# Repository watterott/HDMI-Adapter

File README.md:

# HDMI-Adapter
Universal HDMI/DVI Displays with Touch Panel based on an Adapter with TI TFP401 and Microchip ATmega32u4.

* [TI TFP401A](https://www.ti.com/product/TFP401A) HDMI to RGB Converter
* HDMI compatible (DVI, no Sound, no HDCP, no CEC)
* [Microchip ATmega32U4](https://www.microchip.com/wwwproducts/en/ATMEGA32U4) Microcontroller to control Backlight and Touch Panel (USB HID Mouse)
* LED Backlight Boost Regulator (up to 35V)
* Single 5V Power Supply via MicroUSB connector
* Open-Source and released under the [Creative Commons Attribution Share-Alike License](https://creativecommons.org/licenses/by-sa/4.0/).
* **[Documentation on learn.watterott.com](https://learn.watterott.com)**

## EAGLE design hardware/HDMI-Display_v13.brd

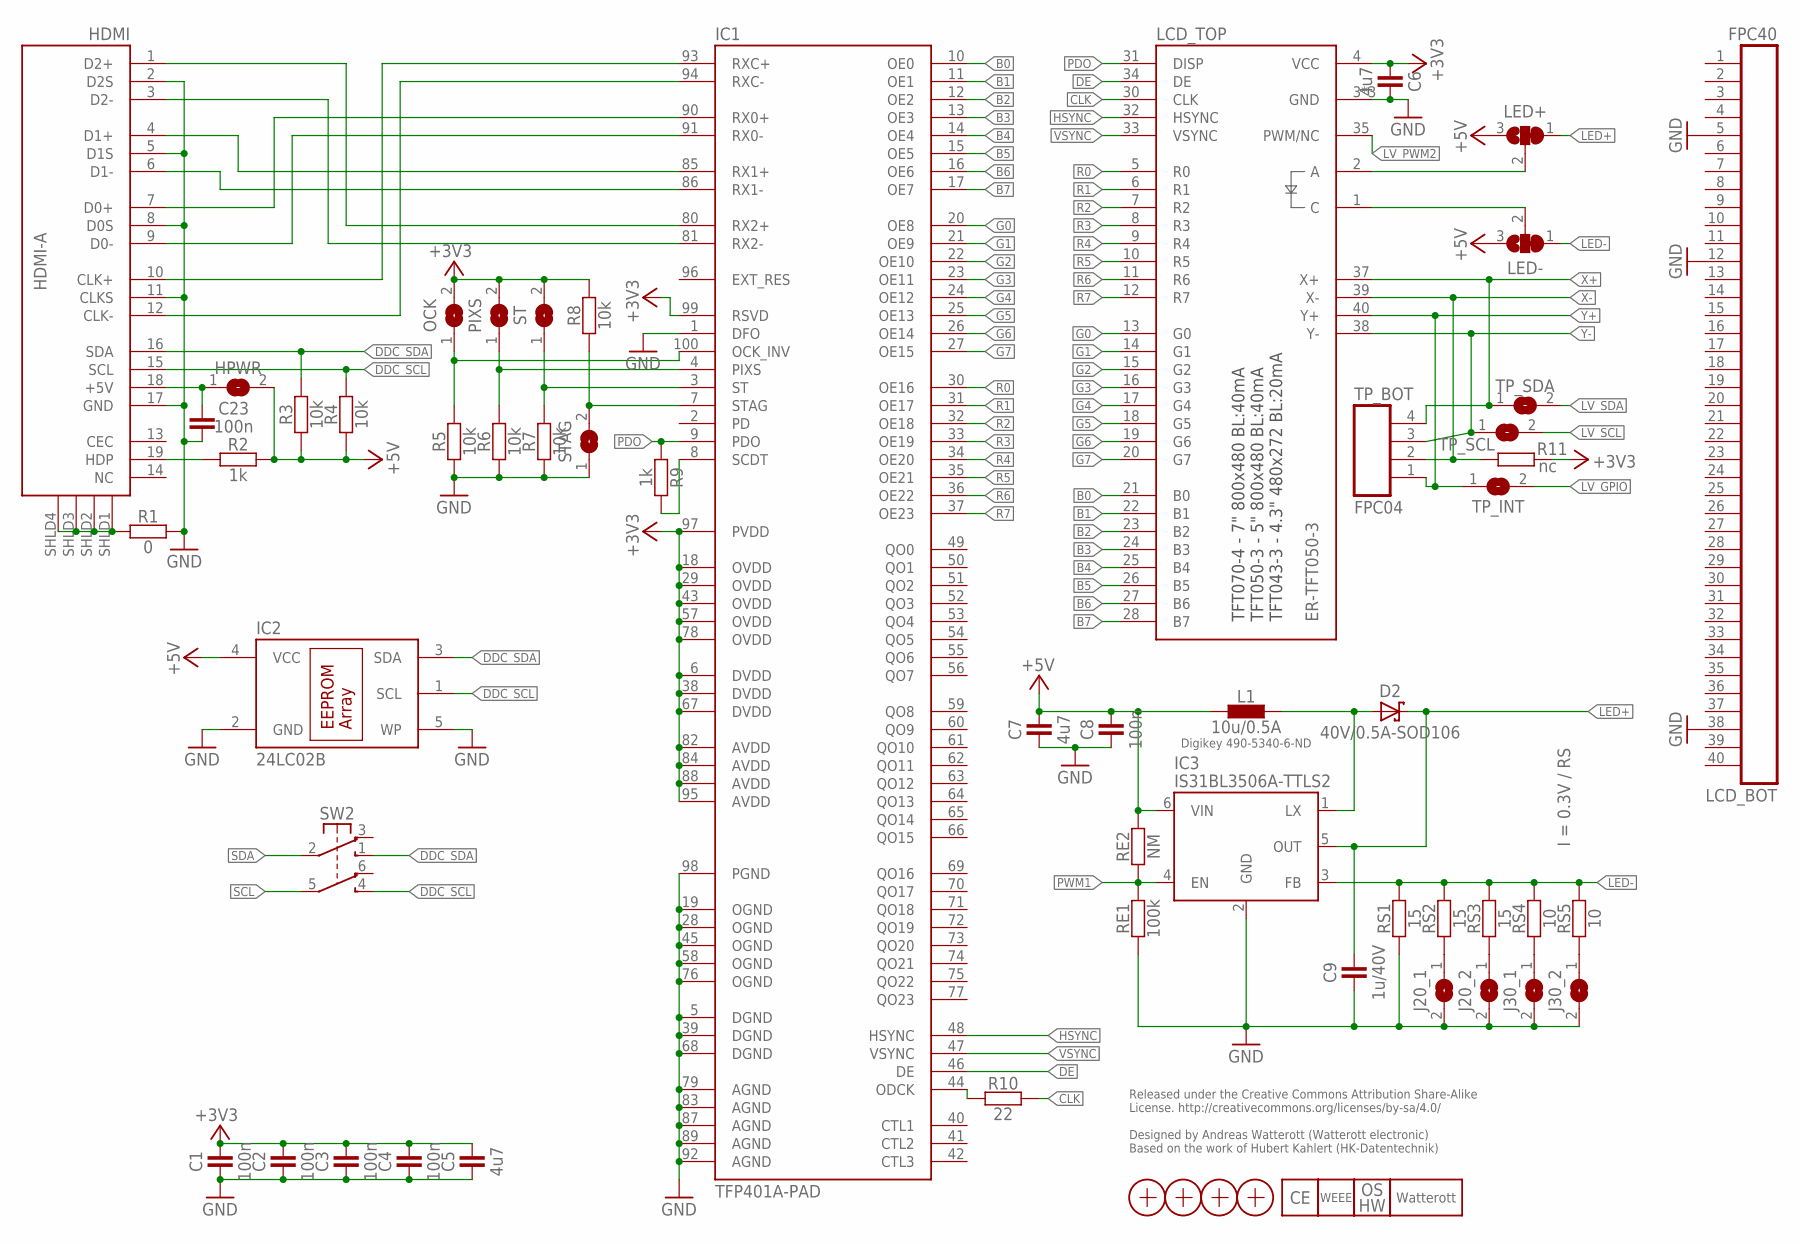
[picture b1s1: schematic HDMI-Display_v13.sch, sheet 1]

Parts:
C1, C2, C3, C4, C8, C23: 100n; C0402
C5, C6, C7: 4u7; C0402
C9: 1u/40V; C0805
D2: 40V/0.5A-SOD106; SOD106
HDMI: HDMI-A; HDMI_10029449
HPWR: JUMPER2-0402
IC1: TFP401A-PAD; TQFP100-PAD
IC2: 24LC02B; SOT23-5
IC3: IS31BL3506A-TTLS2; SOT23-6
J20_1, J20_2, J30_1, J30_2: JUMPER2-0402
L1: 10u/0.5A; L_1212
LCD_BOT: FPC40; FPC40-0.5
LCD_TOP: ER-TFT050-3; FPC40
LED+: JUMPER3-0402
LED-: JUMPER3-0402
LOGO2: LOGO_SPARK-2; SPARK_2MM
LOGO4: LOGO_WEEE-4; WEEE_4MM
LOGO5: LOGO_CE-2; CE_2MM
LOGO6: LOGO_OSHW-2; OSHW_2MM
OCK: JUMPER2-0201-NC; JUMPER2-0201_NC
PIXS: JUMPER2-0201-NC; JUMPER2-0201_NC
R1: 0; C0402
R2, R9: 1k; C0402
R3, R4, R5, R6, R7, R8: 10k; C0402
R10: 22; C0402
R11: nc; C0402
RE1: 100k; C0402
RE2: NM; C0402
RS1, RS2, RS3: 15; C0402
RS4, RS5: 10; C0402
ST: JUMPER2-0201-NC; JUMPER2-0201_NC
STAG: JUMPER2-0201-NC; JUMPER2-0201_NC
SW2: SW-2UM-CUS22B; CUS22B
TP_BOT: FPC04; FPC04-1.0
TP_INT: JUMPER2-0402
TP_SCL: JUMPER2-0402
TP_SDA: JUMPER2-0402
X1, X2, X3, X4: PASSER-07; PASSER_07MM

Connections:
+3V3: C1.2, C2.2, C3.2, C4.2, C5.2, C6.1, IC1.6 (DVDD), IC1.18 (OVDD), IC1.29 (OVDD), IC1.38 (DVDD), IC1.43 (OVDD), IC1.57 (OVDD), IC1.67 (DVDD), IC1.78 (OVDD), IC1.82 (AVDD), IC1.84 (AVDD), IC1.88 (AVDD), IC1.95 (AVDD), IC1.97 (PVDD), IC1.99 (RSVD), LCD_TOP.4 (VCC), OCK.2, PIXS.2, R8.2, R11.2, ST.2; also elsewhere on the board
+5V: C7.2, C8.2, HPWR.2, IC2.4 (VCC), IC3.6 (VIN), L1.1, LED+.3, LED-.3, R2.2, R3.1, R4.1, RE2.2; also elsewhere on the board
B0: IC1.10 (OE0), LCD_TOP.21 (B0)
B1: IC1.11 (OE1), LCD_TOP.22 (B1)
B2: IC1.12 (OE2), LCD_TOP.23 (B2)
B3: IC1.13 (OE3), LCD_TOP.24 (B3)
B4: IC1.14 (OE4), LCD_TOP.25 (B4)
B5: IC1.15 (OE5), LCD_TOP.26 (B5)
B6: IC1.16 (OE6), LCD_TOP.27 (B6)
B7: IC1.17 (OE7), LCD_TOP.28 (B7)
CLK: LCD_TOP.30 (CLK), R10.2
CLK_N: HDMI.12 (CLK-), IC1.94 (RXC-)
CLK_P: HDMI.10 (CLK+), IC1.93 (RXC+)
D0_N: HDMI.9 (D0-), IC1.91 (RX0-)
D0_P: HDMI.7 (D0+), IC1.90 (RX0+)
D1_N: HDMI.6 (D1-), IC1.86 (RX1-)
D1_P: HDMI.4 (D1+), IC1.85 (RX1+)
D2_N: HDMI.3 (D2-), IC1.81 (RX2-)
D2_P: HDMI.1 (D2+), IC1.80 (RX2+)
DDC_SCL: HDMI.15 (SCL), IC2.1 (SCL), R4.2, SW2.4 (S2)
DDC_SDA: HDMI.16 (SDA), IC2.3 (SDA), R3.2, SW2.1 (S1)
DE: IC1.46 (DE), LCD_TOP.34 (DE)
G0: IC1.20 (OE8), LCD_TOP.13 (G0)
G1: IC1.21 (OE9), LCD_TOP.14 (G1)
G2: IC1.22 (OE10), LCD_TOP.15 (G2)
G3: IC1.23 (OE11), LCD_TOP.16 (G3)
G4: IC1.24 (OE12), LCD_TOP.17 (G4)
G5: IC1.25 (OE13), LCD_TOP.18 (G5)
G6: IC1.26 (OE14), LCD_TOP.19 (G6)
G7: IC1.27 (OE15), LCD_TOP.20 (G7)
GND: C1.1, C2.1, C3.1, C4.1, C5.1, C6.2, C7.1, C8.1, C9.1, C23.1, HDMI.2 (D2S), HDMI.5 (D1S), HDMI.8 (D0S), HDMI.11 (CLKS), HDMI.17 (GND), IC1.1 (DFO), IC1.5 (DGND), IC1.19 (OGND), IC1.28 (OGND), IC1.39 (DGND), IC1.45 (OGND), IC1.58 (OGND), IC1.68 (DGND), IC1.76 (OGND), IC1.79 (AGND), IC1.83 (AGND), IC1.87 (AGND), IC1.89 (AGND), IC1.92 (AGND), IC1.98 (PGND), IC2.2 (GND), IC2.5 (WP), IC3.2 (GND), J20_1.2, J20_2.2, J30_1.2, J30_2.2, LCD_BOT.5, LCD_BOT.12, LCD_BOT.38, LCD_TOP.3 (GND), LCD_TOP.29 (GND), LCD_TOP.36 (GND), R1.1, R5.1, R6.1, R7.1, RE1.1, RS1.1, STAG.1; also elsewhere on the board
HDMI_5V: C23.2, HDMI.18 (+5V), HPWR.1
HDMI_DECT: HDMI.19 (HDP), R2.1
HSYNC: IC1.48 (HSYNC), LCD_TOP.32 (HSYNC)
LED+: C9.2, D2.C, IC3.5 (OUT), LED+.1
LED-: IC3.3 (FB), LED-.1, RS1.2, RS2.2, RS3.2, RS4.2, RS5.2
LEDA: LCD_TOP.2 (A), LED+.2
LEDC: LCD_TOP.1 (C), LED-.2
LV_GPIO: TP_INT.2; also elsewhere on the board
LV_PWM2: LCD_TOP.35 (PWM/NC); also elsewhere on the board
LV_SCL: TP_SCL.2; also elsewhere on the board
LV_SDA: TP_SDA.2; also elsewhere on the board
LX: D2.A, IC3.1 (LX), L1.2
unnamed: J20_2.1, RS3.1
unnamed: IC1.44 (ODCK), R10.1
unnamed: J30_1.1, RS4.1
unnamed: J20_1.1, RS2.1
unnamed: J30_2.1, RS5.1
OCKINV: IC1.100 (OCK_INV), OCK.1, R5.2
PDO: IC1.9 (PDO), LCD_TOP.31 (DISP), R9.1
PIXS: IC1.4 (PIXS), PIXS.1, R6.2
PWM1: IC3.4 (EN), RE1.2, RE2.1; also elsewhere on the board
R0: IC1.30 (OE16), LCD_TOP.5 (R0)
R1: IC1.31 (OE17), LCD_TOP.6 (R1)
R2: IC1.32 (OE18), LCD_TOP.7 (R2)
R3: IC1.33 (OE19), LCD_TOP.8 (R3)
R4: IC1.34 (OE20), LCD_TOP.9 (R4)
R5: IC1.35 (OE21), LCD_TOP.10 (R5)
R6: IC1.36 (OE22), LCD_TOP.11 (R6)
R7: IC1.37 (OE23), LCD_TOP.12 (R7)
SCDT: IC1.8 (SCDT), R9.2
SCL: SW2.5 (P2); also elsewhere on the board
SDA: SW2.2 (P1); also elsewhere on the board
SHLD3: HDMI.SHLD1 (SHLD), HDMI.SHLD2 (SHLD), HDMI.SHLD3 (SHLD), HDMI.SHLD4 (SHLD), R1.2
ST: IC1.3 (ST), R7.2, ST.1
STAG: IC1.7 (STAG), R8.1, STAG.2
VSYNC: IC1.47 (VSYNC), LCD_TOP.33 (VSYNC)
X+: LCD_TOP.37 (X+), TP_BOT.4, TP_SDA.1; also elsewhere on the board
X-: LCD_TOP.39 (X-), R11.1, TP_BOT.2; also elsewhere on the board
Y+: LCD_TOP.40 (Y+), TP_BOT.1, TP_INT.1; also elsewhere on the board
Y-: LCD_TOP.38 (Y-), TP_BOT.3, TP_SCL.1; also elsewhere on the board

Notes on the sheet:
I = 0.3V / RS
Digikey 490-5340-6-ND
Released under the Creative Commons Attribution Share-Alike License. http://creativecommons.org/licenses/by-sa/4.0/ Designed by Andreas Watterott (Watterott electronic) Based on the work of Hubert Kahlert (HK-Datentechnik)
TFT070-4 - 7" 800x480 BL:40mA TFT050-3 - 5" 800x480 BL:40mA TFT043-3 - 4.3" 480x272 BL:20mA

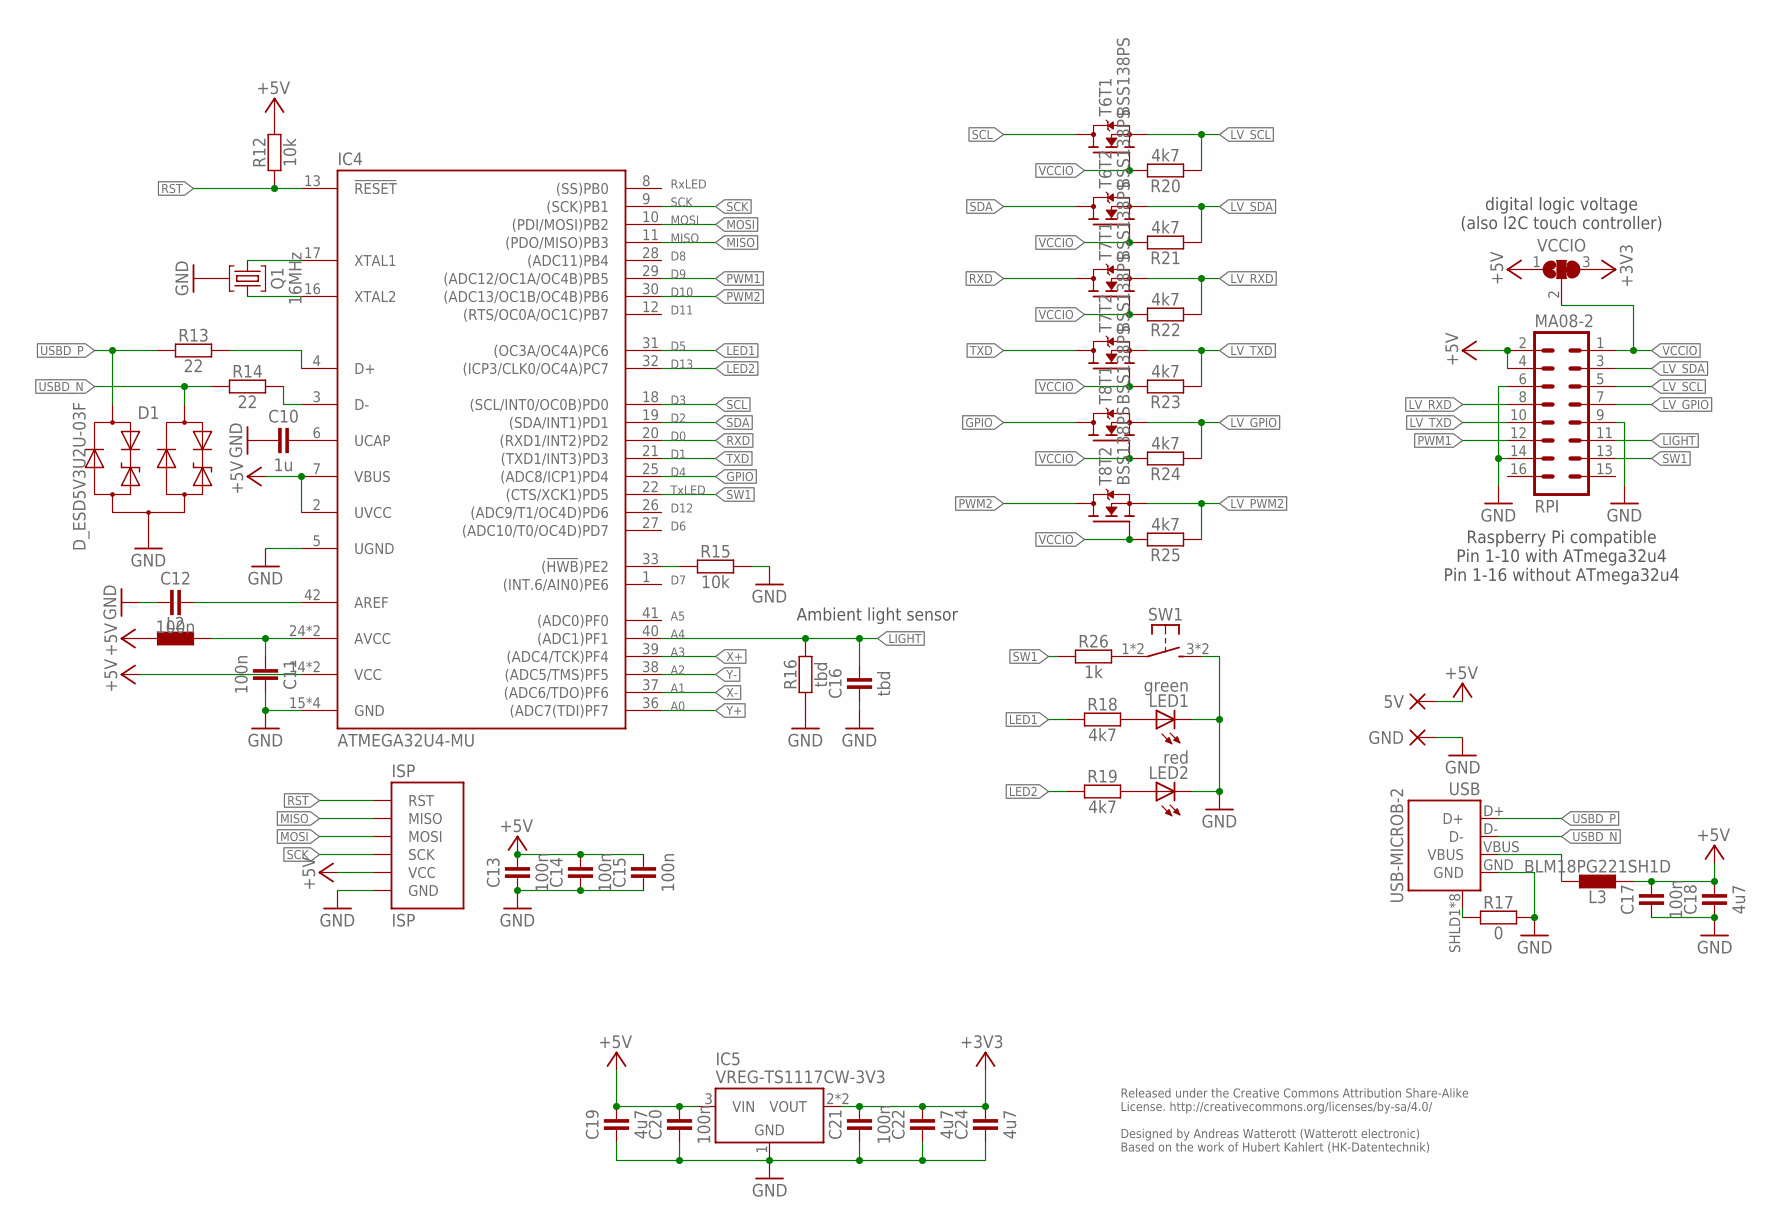
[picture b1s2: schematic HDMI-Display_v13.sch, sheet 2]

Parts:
5V: PAD-1.27X2.54_NC
C10: 1u; C0402
C11, C12, C13, C14, C15, C17, C20, C21: 100n; C0402
C16: tbd; C0402
C18, C19, C22, C24: 4u7; C0402
D1: D_ESD5V3U2U-03F; SOT723
GND: PAD-1.27X2.54_NC
IC4: ATMEGA32U4-MU; QFN44
IC5: VREG-TS1117CW-3V3; SOT223
ISP: ISP; ISP-2X3
L2: INDUCTOR-0603; C0603
L3: BLM18PG221SH1D; C0603
LED1: green; C0603
LED2: red; C0603
Q1: 16MHz; CRYSTAL_32X13
R12, R15: 10k; C0402
R13, R14: 22; C0402
R16: tbd; C0402
R17: 0; C0402
R18, R19, R20, R21, R22, R23, R24, R25: 4k7; C0402
R26: 1k; C0402
RPI: MA08-2
SW1: SW-TACTILE-PTS840P; PTS840P
T6, T7, T8: BSS138PS; SOT363
USB: USB-MICROB-2; USB-MICROB-10118194
VCCIO: JUMPER3-0402

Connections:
+3V3: C21.2, C22.2, C24.2, IC5.2 (VOUT), IC5.4 (VOUT), VCCIO.3; also elsewhere on the board
+5V: 5V.1, C13.2, C14.2, C15.2, C17.2, C18.2, C19.2, C20.2, IC4.2 (UVCC), IC4.7 (VBUS), IC4.14 (VCC), IC4.34 (VCC), IC5.3 (VIN), ISP.VCC, L2.1, L3.1, R12.2, RPI.2, RPI.4, VCCIO.1; also elsewhere on the board
AREF: C12.2, IC4.42 (AREF)
AVCC: C11.1, IC4.24 (AVCC), IC4.44 (AVCC), L2.2
D_N: IC4.3 (D-), R14.2
D_P: IC4.4 (D+), R13.2
GND: C10.1, C11.2, C12.1, C13.1, C14.1, C15.1, C16.1, C17.1, C18.1, C19.1, C20.1, C21.1, C22.1, C24.1, D1.3 (A), GND.1, IC4.5 (UGND), IC4.15 (GND), IC4.23 (GND), IC4.35 (GND), IC4.43 (GND), IC5.1 (GND), ISP.GND, LED1.C, LED2.C, Q1.GND, R15.2, R16.1, R17.1, RPI.6, RPI.9, RPI.14, SW1.3 (S1), SW1.4 (S1), USB.GND; also elsewhere on the board
GPIO: IC4.25 ((ADC8/ICP1)PD4), T8.6 (D)
HWB: IC4.33 ((!HWB!)PE2), R15.1
LED1: IC4.31 ((OC3A/OC4A)PC6), R18.1
LED2: IC4.32 ((ICP3/CLK0/OC4A)PC7), R19.1
LIGHT: C16.2, IC4.40 ((ADC1)PF1), R16.2, RPI.11
LV_GPIO: R24.1, RPI.7, T8.1 (S); also elsewhere on the board
LV_PWM2: R25.1, T8.4 (S); also elsewhere on the board
LV_RXD: R22.1, RPI.8, T7.1 (S)
LV_SCL: R20.1, RPI.5, T6.1 (S); also elsewhere on the board
LV_SDA: R21.1, RPI.3, T6.4 (S); also elsewhere on the board
LV_TXD: R23.1, RPI.10, T7.4 (S)
MISO: IC4.11 ((PDO/MISO)PB3), ISP.MISO
MOSI: IC4.10 ((PDI/MOSI)PB2), ISP.MOSI
unnamed: R26.2, SW1.1, SW1.2 (P1)
unnamed: LED1.A, R18.2
unnamed: LED2.A, R19.2
PWM1: IC4.29 ((ADC12/OC1A/OC4B)PB5), RPI.12; also elsewhere on the board
PWM2: IC4.30 ((ADC13/OC1B/OC4B)PB6), T8.3 (D)
RST: IC4.13 (!RESET), ISP.RST, R12.1
RXD: IC4.20 ((RXD1/INT2)PD2), T7.6 (D)
SCK: IC4.9 ((SCK)PB1), ISP.SCK
SCL: IC4.18 ((SCL/INT0/OC0B)PD0), T6.6 (D); also elsewhere on the board
SDA: IC4.19 ((SDA/INT1)PD1), T6.3 (D); also elsewhere on the board
SHLD1: R17.2, USB.SHLD1 (SHIELD), USB.SHLD2 (SHIELD), USB.SHLD3 (SHIELD), USB.SHLD4 (SHIELD), USB.SHLD5 (SHIELD), USB.SHLD6 (SHIELD), USB.SHLD7 (SHIELD), USB.SHLD8 (SHIELD)
SW1: IC4.22 ((CTS/XCK1)PD5), R26.1, RPI.13
TXD: IC4.21 ((TXD1/INT3)PD3), T7.3 (D)
UCAP: C10.2, IC4.6 (UCAP)
USBD_N: D1.2 (C2), R14.1, USB.D-
USBD_P: D1.1 (C1), R13.1, USB.D+
VBUS: L3.2, USB.VBUS
VCCIO: R20.2, R21.2, R22.2, R23.2, R24.2, R25.2, RPI.1, T6.2 (G), T6.5 (G), T7.2 (G), T7.5 (G), T8.2 (G), T8.5 (G), VCCIO.2
X+: IC4.39 ((ADC4/TCK)PF4); also elsewhere on the board
X-: IC4.37 ((ADC6/TDO)PF6); also elsewhere on the board
XTAL1: IC4.17 (XTAL1), Q1.2
XTAL2: IC4.16 (XTAL2), Q1.1
Y+: IC4.36 ((ADC7(TDI)PF7); also elsewhere on the board
Y-: IC4.38 ((ADC5/TMS)PF5); also elsewhere on the board

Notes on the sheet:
Ambient light sensor
Released under the Creative Commons Attribution Share-Alike License. http://creativecommons.org/licenses/by-sa/4.0/ Designed by Andreas Watterott (Watterott electronic) Based on the work of Hubert Kahlert (HK-Datentechnik)
TxLED
D12
D13
RxLED
SCK
MOSI
MISO
D10
D11
Raspberry Pi compatible Pin 1-10 with ATmega32u4 Pin 1-16 without ATmega32u4
digital logic voltage (also I2C touch controller)

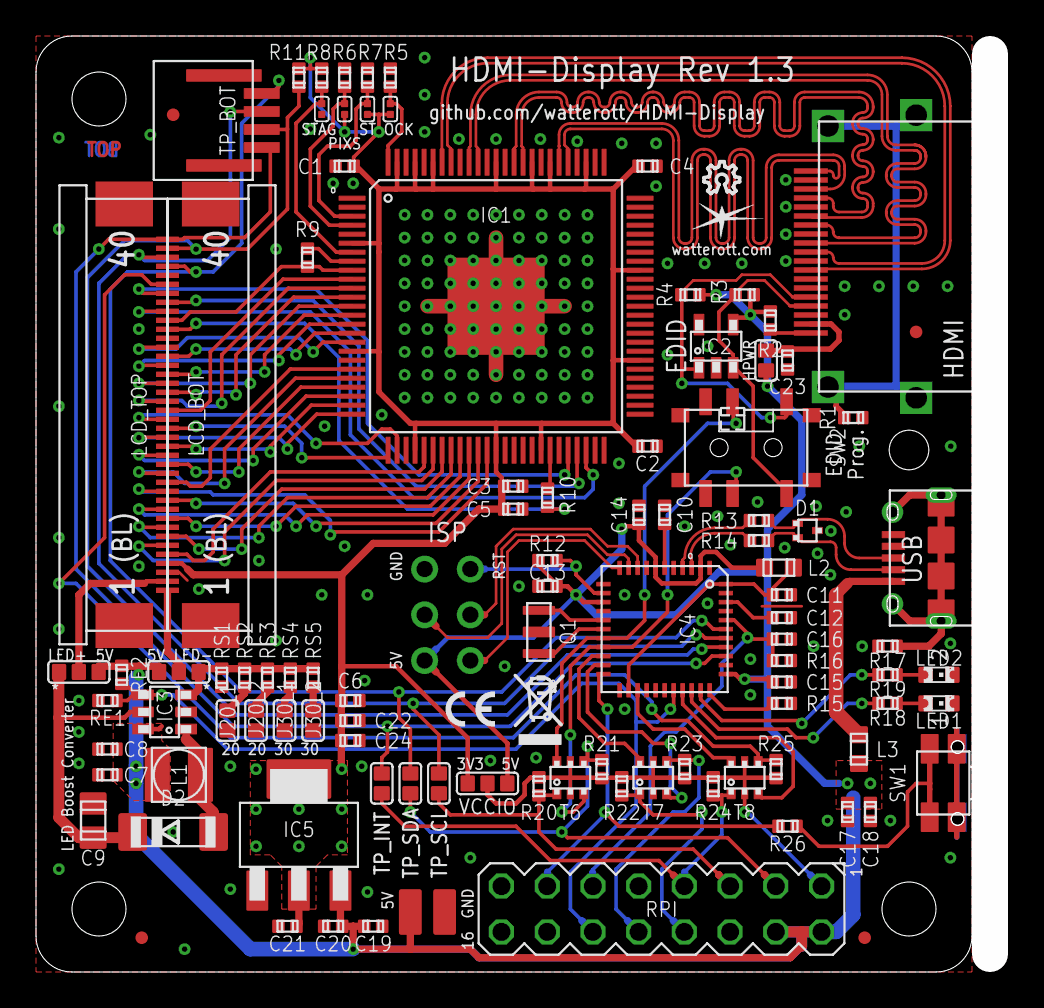
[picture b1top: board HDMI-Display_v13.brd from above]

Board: 2 copper layers, 52.0 x 50.0 mm, 107 parts (0 on the bottom side), 101 nets.

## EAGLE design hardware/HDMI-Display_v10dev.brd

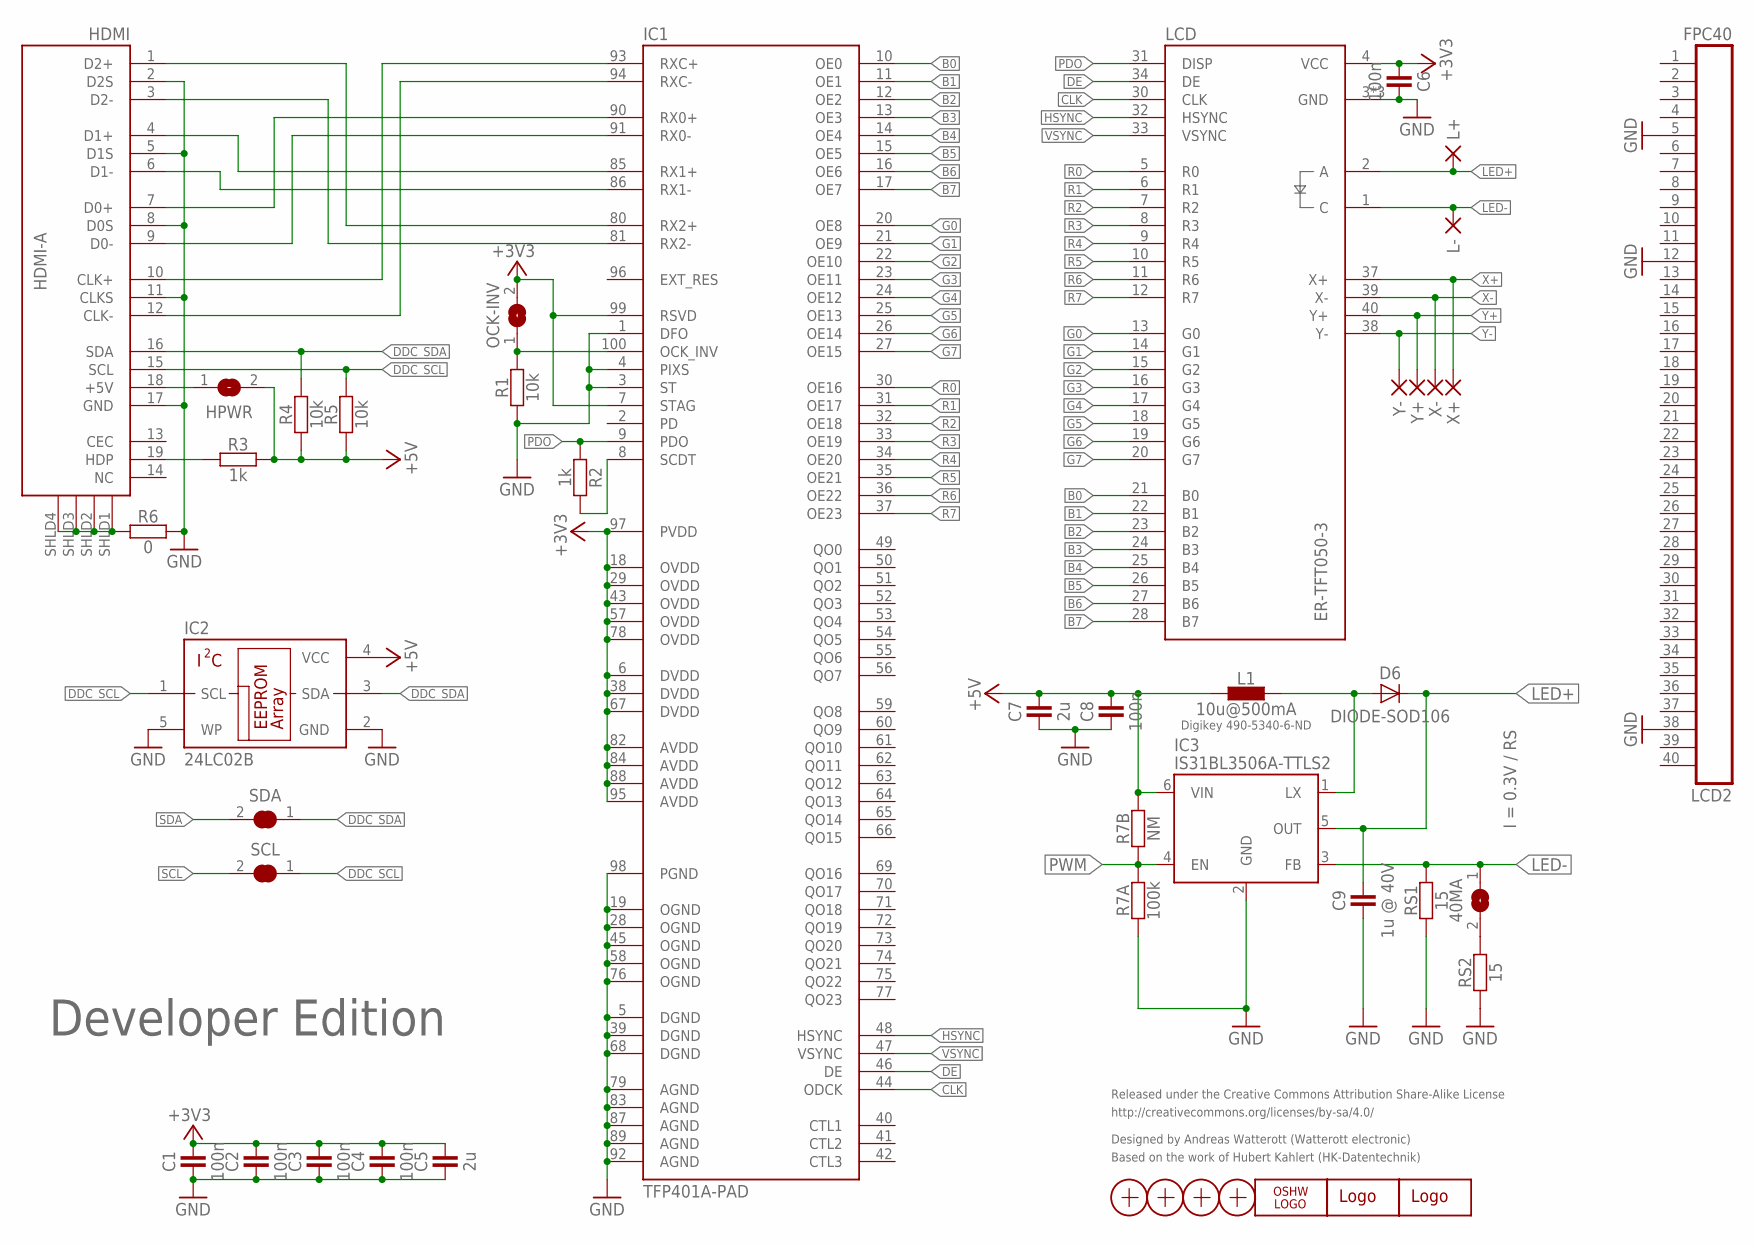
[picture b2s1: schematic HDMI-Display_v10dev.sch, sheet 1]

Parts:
40MA: JUMPER2
C1, C2, C3, C4, C6, C8: 100n; R0402
C5, C7: 2u; R0402
C9: 1u @ 40V; R0805
D6: DIODE-SOD106; SOD106
HDMI: HDMI-A; HDMI_10029449
HPWR: JUMPER2
IC1: TFP401A-PAD; TQFP100-PAD
IC2: 24LC02B; SOT23-5
IC3: IS31BL3506A-TTLS2; SOT23-6
L1: 10u@500mA; L_1212
L+: PAD-0.80X1.60_NC
L-: PAD-0.80X1.60_NC
LCD: ER-TFT050-3; FPC40
LCD2: FPC40
LOGO1: OSHW_LOGOX0070; OSHW_6X70
LOGO2: LOGO-PLACE; LOGO_TPLACE
LOGO3: LOGO-S_PLACE_S; SPARK_TPLACE_S
OCK-INV: JUMPER2
R1, R4, R5: 10k; R0402
R2, R3: 1k; R0402
R6: 0; R0402
R7A: 100k; R0402
R7B: NM; R0402
RS1, RS2: 15; R0402
SCL: JUMPER2
SDA: JUMPER2
X1, X2, X3, X4: PASSER-07; PASSER_07MM
X+: PAD-0.80X1.60_NC
X-: PAD-0.80X1.60_NC
Y+: PAD-0.80X1.60_NC
Y-: PAD-0.80X1.60_NC

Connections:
+3V3: C1.2, C2.2, C3.2, C4.2, C5.2, C6.1, IC1.6 (DVDD), IC1.7 (STAG), IC1.18 (OVDD), IC1.29 (OVDD), IC1.38 (DVDD), IC1.43 (OVDD), IC1.57 (OVDD), IC1.67 (DVDD), IC1.78 (OVDD), IC1.82 (AVDD), IC1.84 (AVDD), IC1.88 (AVDD), IC1.95 (AVDD), IC1.97 (PVDD), IC1.99 (RSVD), LCD.4 (VCC), OCK-INV.2; also elsewhere on the board
+5V: C7.2, C8.2, HPWR.2, IC2.4 (VCC), IC3.6 (VIN), L1.1, R3.2, R4.1, R5.1, R7B.2; also elsewhere on the board
B0: IC1.10 (OE0), LCD.21 (B0)
B1: IC1.11 (OE1), LCD.22 (B1)
B2: IC1.12 (OE2), LCD.23 (B2)
B3: IC1.13 (OE3), LCD.24 (B3)
B4: IC1.14 (OE4), LCD.25 (B4)
B5: IC1.15 (OE5), LCD.26 (B5)
B6: IC1.16 (OE6), LCD.27 (B6)
B7: IC1.17 (OE7), LCD.28 (B7)
CLK: IC1.44 (ODCK), LCD.30 (CLK)
CLK_N: HDMI.12 (CLK-), IC1.94 (RXC-)
CLK_P: HDMI.10 (CLK+), IC1.93 (RXC+)
D0_N: HDMI.9 (D0-), IC1.91 (RX0-)
D0_P: HDMI.7 (D0+), IC1.90 (RX0+)
D1_N: HDMI.6 (D1-), IC1.86 (RX1-)
D1_P: HDMI.4 (D1+), IC1.85 (RX1+)
D2_N: HDMI.3 (D2-), IC1.81 (RX2-)
D2_P: HDMI.1 (D2+), IC1.80 (RX2+)
DDC_SCL: HDMI.15 (SCL), IC2.1 (SCL), R5.2, SCL.1
DDC_SDA: HDMI.16 (SDA), IC2.3 (SDA), R4.2, SDA.1
DE: IC1.46 (DE), LCD.34 (DE)
G0: IC1.20 (OE8), LCD.13 (G0)
G1: IC1.21 (OE9), LCD.14 (G1)
G2: IC1.22 (OE10), LCD.15 (G2)
G3: IC1.23 (OE11), LCD.16 (G3)
G4: IC1.24 (OE12), LCD.17 (G4)
G5: IC1.25 (OE13), LCD.18 (G5)
G6: IC1.26 (OE14), LCD.19 (G6)
G7: IC1.27 (OE15), LCD.20 (G7)
GND: C1.1, C2.1, C3.1, C4.1, C5.1, C6.2, C7.1, C8.1, C9.1, HDMI.2 (D2S), HDMI.5 (D1S), HDMI.8 (D0S), HDMI.11 (CLKS), HDMI.17 (GND), IC1.1 (DFO), IC1.3 (ST), IC1.4 (PIXS), IC1.5 (DGND), IC1.19 (OGND), IC1.28 (OGND), IC1.39 (DGND), IC1.45 (OGND), IC1.58 (OGND), IC1.68 (DGND), IC1.76 (OGND), IC1.79 (AGND), IC1.83 (AGND), IC1.87 (AGND), IC1.89 (AGND), IC1.92 (AGND), IC1.98 (PGND), IC2.2 (GND), IC2.5 (WP), IC3.2 (GND), LCD.3 (GND), LCD.29 (GND), LCD.36 (GND), LCD2.5, LCD2.12, LCD2.38, R1.1, R6.1, R7A.1, RS1.1, RS2.1; also elsewhere on the board
HDMI_5V: HDMI.18 (+5V), HPWR.1
HDMI_DECT: HDMI.19 (HDP), R3.1
HSYNC: IC1.48 (HSYNC), LCD.32 (HSYNC)
LED+: C9.2, D6.C, IC3.5 (OUT), L+.1, LCD.2 (A)
LED-: 40MA.1, IC3.3 (FB), L-.1, LCD.1 (C), RS1.2
LX: D6.A, IC3.1 (LX), L1.2
unnamed: 40MA.2, RS2.2
unnamed: IC1.100 (OCK_INV), OCK-INV.1, R1.2
PDO: IC1.9 (PDO), LCD.31 (DISP), R2.1
PWM: IC3.4 (EN), R7A.2, R7B.1; also elsewhere on the board
R0: IC1.30 (OE16), LCD.5 (R0)
R1: IC1.31 (OE17), LCD.6 (R1)
R2: IC1.32 (OE18), LCD.7 (R2)
R3: IC1.33 (OE19), LCD.8 (R3)
R4: IC1.34 (OE20), LCD.9 (R4)
R5: IC1.35 (OE21), LCD.10 (R5)
R6: IC1.36 (OE22), LCD.11 (R6)
R7: IC1.37 (OE23), LCD.12 (R7)
SCDT: IC1.8 (SCDT), R2.2
SCL: SCL.2; also elsewhere on the board
SDA: SDA.2; also elsewhere on the board
SHLD3: HDMI.SHLD1 (SHLD), HDMI.SHLD2 (SHLD), HDMI.SHLD3 (SHLD), HDMI.SHLD4 (SHLD), R6.2
VSYNC: IC1.47 (VSYNC), LCD.33 (VSYNC)
X+: LCD.37 (X+), X+.1; also elsewhere on the board
X-: LCD.39 (X-), X-.1; also elsewhere on the board
Y+: LCD.40 (Y+), Y+.1; also elsewhere on the board
Y-: LCD.38 (Y-), Y-.1; also elsewhere on the board

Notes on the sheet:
I = 0.3V / RS
Digikey 490-5340-6-ND
Released under the Creative Commons Attribution Share-Alike License
http://creativecommons.org/licenses/by-sa/4.0/
Designed by Andreas Watterott (Watterott electronic)
Based on the work of Hubert Kahlert (HK-Datentechnik)
Developer Edition

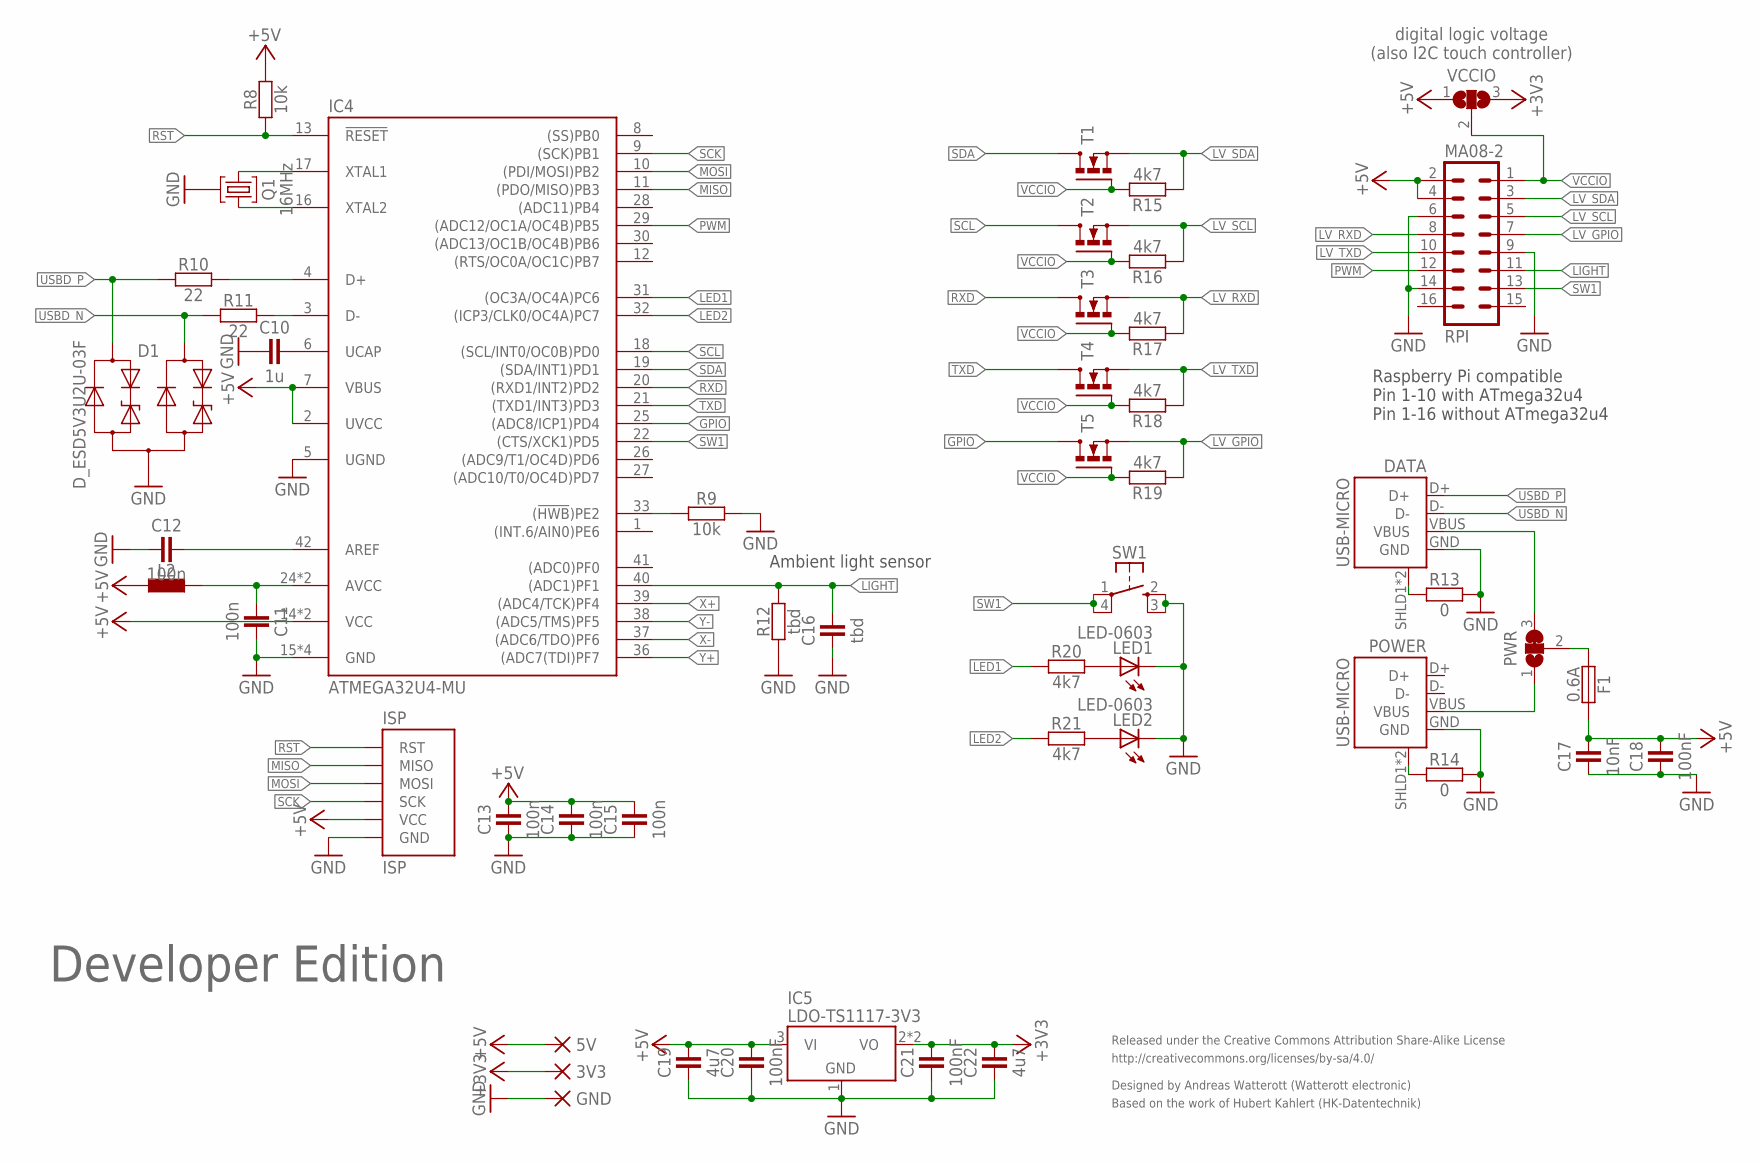
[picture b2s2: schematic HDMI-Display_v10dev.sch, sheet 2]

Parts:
3V3, 5V: PAD-1.27X2.54_NC
C10: 1u; R0402
C11, C12, C13, C14, C15: 100n; R0402
C16: tbd; R0402
C17: 10nF; R0402
C18, C20, C21: 100nF; R0402
C19, C22: 4u7; R0402
D1: D_ESD5V3U2U-03F; SOT723
DATA: USB-MICRO; USB-MICRO-10103594
F1: 0.6A; R0805
GND: PAD-1.27X2.54_NC
IC4: ATMEGA32U4-MU; QFN44
IC5: LDO-TS1117-3V3; SOT223
ISP: ISP
L2: INDUCTOR-0603; R0603
LED1, LED2: LED-0603; LED_0603
POWER: USB-MICRO; USB-MICRO-10103594
PWR: JUMPER3
Q1: 16MHz; CRYSTAL_32X13
R8, R9: 10k; R0402
R10, R11: 22; R0402
R12: tbd; R0402
R13, R14: 0; R0402
R15, R16, R17, R18, R19, R20, R21: 4k7; R0402
RPI: MA08-2
SW1: SW-TACTILE-TL3315; SW_TL3315N
T1, T2, T3, T4, T5: MOSFET-N-SOT23; SOT23
VCCIO: JUMPER3-NOCREAM; JUMPER3_NC

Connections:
+3V3: 3V3.1, C21.2, C22.2, IC5.2 (VO), IC5.4 (VO), VCCIO.3; also elsewhere on the board
+5V: 5V.1, C13.2, C14.2, C15.2, C17.2, C18.2, C19.2, C20.2, F1.1, IC4.2 (UVCC), IC4.7 (VBUS), IC4.14 (VCC), IC4.34 (VCC), IC5.3 (VI), ISP.VCC, L2.1, R8.2, RPI.2, RPI.4, VCCIO.1; also elsewhere on the board
AREF: C12.2, IC4.42 (AREF)
AVCC: C11.1, IC4.24 (AVCC), IC4.44 (AVCC), L2.2
D_N: IC4.3 (D-), R11.2
D_P: IC4.4 (D+), R10.2
GND: C10.1, C11.2, C12.1, C13.1, C14.1, C15.1, C16.1, C17.1, C18.1, C19.1, C20.1, C21.1, C22.1, D1.3 (A), DATA.GND, GND.1, IC4.5 (UGND), IC4.15 (GND), IC4.23 (GND), IC4.35 (GND), IC4.43 (GND), IC5.1 (GND), ISP.GND, LED1.C, LED2.C, POWER.GND, Q1.GND, R9.2, R12.1, R13.1, R14.1, RPI.6, RPI.9, RPI.14, SW1.2 (S1), SW1.3 (S2); also elsewhere on the board
GPIO: IC4.25 ((ADC8/ICP1)PD4), T5.3 (D)
HWB: IC4.33 ((!HWB!)PE2), R9.1
LED1: IC4.31 ((OC3A/OC4A)PC6), R20.1
LED2: IC4.32 ((ICP3/CLK0/OC4A)PC7), R21.1
LIGHT: C16.2, IC4.40 ((ADC1)PF1), R12.2, RPI.11
LV_GPIO: R19.1, RPI.7, T5.2 (S)
LV_RXD: R17.1, RPI.8, T3.2 (S)
LV_SCL: R16.1, RPI.5, T2.2 (S)
LV_SDA: R15.1, RPI.3, T1.2 (S)
LV_TXD: R18.1, RPI.10, T4.2 (S)
MISO: IC4.11 ((PDO/MISO)PB3), ISP.MISO
MOSI: IC4.10 ((PDI/MOSI)PB2), ISP.MOSI
unnamed: C10.2, IC4.6 (UCAP)
unnamed: F1.2, PWR.2
unnamed: LED1.A, R20.2
unnamed: LED2.A, R21.2
PWM: IC4.29 ((ADC12/OC1A/OC4B)PB5), RPI.12; also elsewhere on the board
RST: IC4.13 (!RESET), ISP.RST, R8.1
RXD: IC4.20 ((RXD1/INT2)PD2), T3.3 (D)
SCK: IC4.9 ((SCK)PB1), ISP.SCK
SCL: IC4.18 ((SCL/INT0/OC0B)PD0), T2.3 (D); also elsewhere on the board
SDA: IC4.19 ((SDA/INT1)PD1), T1.3 (D); also elsewhere on the board
SHLD1: DATA.SHLD1 (SHIELD), DATA.SHLD2 (SHIELD), R13.2
SHLD2: POWER.SHLD1 (SHIELD), POWER.SHLD2 (SHIELD), R14.2
SW1: IC4.22 ((CTS/XCK1)PD5), RPI.13, SW1.1, SW1.4 (P2)
TXD: IC4.21 ((TXD1/INT3)PD3), T4.3 (D)
USBD_N: D1.2 (C2), DATA.D-, R11.1
USBD_P: D1.1 (C1), DATA.D+, R10.1
VBUS: DATA.VBUS, PWR.3
VBUS_PWR: POWER.VBUS, PWR.1
VCCIO: R15.2, R16.2, R17.2, R18.2, R19.2, RPI.1, T1.1 (G), T2.1 (G), T3.1 (G), T4.1 (G), T5.1 (G), VCCIO.2
X+: IC4.39 ((ADC4/TCK)PF4); also elsewhere on the board
X-: IC4.37 ((ADC6/TDO)PF6); also elsewhere on the board
XTAL1: IC4.17 (XTAL1), Q1.2
XTAL2: IC4.16 (XTAL2), Q1.1
Y+: IC4.36 ((ADC7(TDI)PF7); also elsewhere on the board
Y-: IC4.38 ((ADC5/TMS)PF5); also elsewhere on the board

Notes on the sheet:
Ambient light sensor
Released under the Creative Commons Attribution Share-Alike License
http://creativecommons.org/licenses/by-sa/4.0/
Designed by Andreas Watterott (Watterott electronic)
Based on the work of Hubert Kahlert (HK-Datentechnik)
Raspberry Pi compatible Pin 1-10 with ATmega32u4 Pin 1-16 without ATmega32u4
Developer Edition
digital logic voltage (also I2C touch controller)

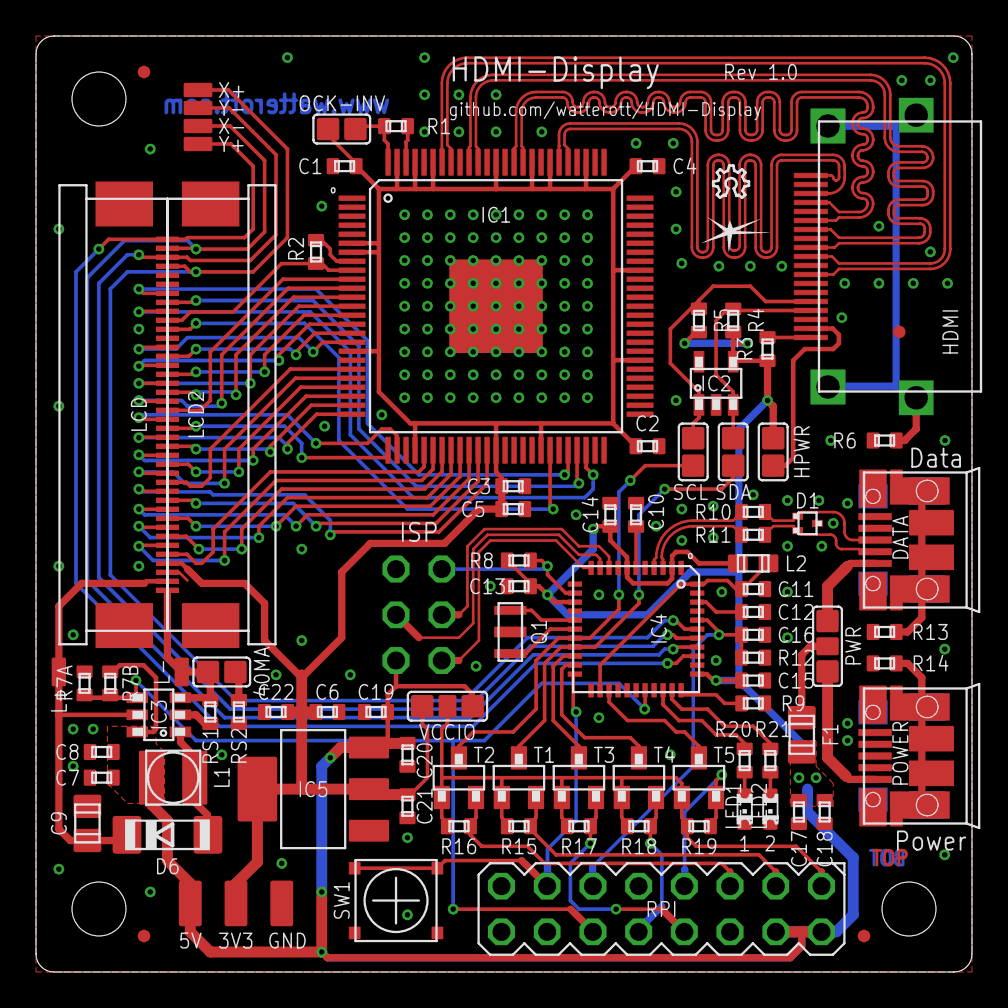
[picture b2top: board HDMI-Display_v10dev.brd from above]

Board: 2 copper layers, 52.0 x 52.0 mm, 95 parts (1 on the bottom side), 92 nets.

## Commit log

2014-12-10 added readme
2015-01-10 added layout and schematics
2015-01-10 added EDID data
2015-01-10 added image
2015-01-11 updated docu and added examples
2015-01-11 updated readme and docu
2015-01-11 added new EDID
2015-01-11 updated schematics
2015-01-14 updated docu
2015-01-16 added touchpanel firmware
2015-01-22 updated installation infos
2015-01-27 updated display list
2015-01-27 updated examples
2015-01-28 updated layout and schematics
2015-01-29 support for Arduino 1.5
2015-02-04 updated EDID data
2015-02-09 added FT5x06 (capacitive touch controller) support
2015-02-10 updated EDID-Prog
2015-02-10 updated firmware for Arduino v1.6
2015-02-10 updated HY070CTP-A EDID
2015-02-11 updated image
2015-02-12 touchpanel and screensaver bugfix
2015-02-14 updated displays
2015-02-17 updated firmware
2015-02-21 added axes invertation+swapping and touchpanel detection
2015-02-22 moved settings to config.h
2015-02-22 bugfix: orientation not set on startup
2015-02-26 updated backlight current
2015-03-05 cleaned-up code
2015-03-05 typo fixes
2015-03-13 no mouse data on screensaver exit
2015-03-13 updated board support package
2015-03-18 updated register info
2015-03-18 bugfix touchpanel orientation
2015-03-25 added pre-built firmware
2015-04-03 added 1024x600 EDID data
2015-04-08 updated schematics/display info
2015-04-11 added option to map mouse coordinates to screen coordinates
2015-04-12 optimized and cleaned up code
2015-04-29 code cleanup renamed moveAbs to moveAbsolute
2015-04-29 code cleanup
2015-05-17 updated docu and readme
2015-06-05 updated patches
2015-07-02 typo fix
2015-07-02 backlight level check added more display types
2015-07-15 added resolution to AT command
2015-07-31 updated infos
2015-08-19 added 2nd pwm pin (pcb rev 1.1)
2015-08-21 changed path structure
2015-08-21 updated links
2015-08-21 updated example
2015-08-26 added rev 1.1 schematics and layout
2015-08-26 overflow bugfix
2015-09-11 updated schematics and docu
2015-09-12 updated docu and image
2015-09-24 minor changes and bugfix in backlight.cpp
2015-09-25 updated display infos
2015-11-11 updated firmware for new pluggable USB core (IDE v1.6.6+)
2015-11-11 v1.50 because of new USB core
2015-11-29 Fixed a few warnings
2015-11-29 Added HID-Project support
2015-12-03 code clean-up
2015-12-20 rewrite to use own TWI/I2C functions
2015-12-22 send mouse clicks periodically
2015-12-22 added watchdog and minor optimizations
2016-01-13 Fixed Touch function
2016-01-13 Added error that required config edit
2016-01-13 Enabled error message
2016-01-13 Version 2.11
2016-01-13 Moved mouse press to fix new press position
2016-01-15 added HID-Project support
    https://github.com/NicoHood/HID
2016-02-04 updated schematics and layout
2016-02-05 screen size and EDID change need no firmware reflash
2016-02-28 udpated readme and docu
2016-03-23 deactivate screensaver when touchpanel is off
2016-04-04 added offset for capacitive touchpanels
2016-04-12 updated pin info
2016-06-30 added register info
2016-07-05 updated license info
2016-07-29 write EDID, when button is pressed on startup set backlight brightness on change
2016-08-19 added HYCON HY461X touch controller
2016-08-19 added gesture debug info
2016-08-21 check touch controller at about 8Hz
2016-08-21 faster wakeup
2016-08-22 added define for minimum TWI frequency
2016-08-25 I2C/TWI frequency bugfix
2016-10-23 only red LED on during EEPROM programming
2017-04-11 added rev 1.2
2017-07-30 moved docu to docs
2018-01-30 moved files
2018-05-01 added rev 1.3
2018-12-02 updated settings
2019-05-12 updated license
